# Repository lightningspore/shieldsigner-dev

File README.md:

# ShieldSigner

An open-hardware smartcard signing device built around the Luckfox Pico Mini, a 2.8-inch SPI display, and physical controls.

[Hardware](hardware/README.md) · [Build guides](docs/README.md) · [Firmware](docs/FIRMWARE-ARTIFACTS.md) · [Website](https://shieldsigner.dev/) · [Contributing](CONTRIBUTING.md)

The **main PCB is the four-layer, eight-pin display carrier with an alternate 14-pin socket in [`kicad/`](kicad/)**. Open [the KiCad project](kicad/SeedSigner-Plus-smartcard-pico.kicad_pro) to edit its schematic or layout. Its previews, assembly data, sourcing information and review reports live in [`hardware/`](hardware/README.md).

## How the pieces fit

ShieldSigner is an offline Bitcoin signer: a wallet on another machine prepares a
transaction, the signer reviews and signs it, and the result travels back by QR
code. The project has three parts:

| Part | What it is | State |
|---|---|---|
| **Hardware** | The carrier PCB in [`kicad/`](kicad/) and the printed [enclosure](docs/ENCLOSURE.md). A 240×240 display/button bench board is used for firmware development. | First-article design; digital checks pass, physical bring-up open |
| **Linux firmware** | SeedSigner OS (Buildroot) running the [LVGL frontend](firmware/lvgl-app/README.md) over the pinned ShieldSigner Python app, with the Rust camera stack in [`firmware/rkaiq-rs`](firmware/rkaiq-rs/). | Current development image, bench-tested; see [firmware status](docs/FIRMWARE-STATUS.md) |
| **Bare-metal firmware** | The same pinned app and LVGL screens on MicroPython over a Rust `no_std` runtime, with no Linux. Boots straight into the app from a ~4 MiB microSD image. | Experimental; most workflows verified on the bench board, see [`baremetal/`](baremetal/README.md) |

Both firmware paths share the application source pin, the LVGL screen library, the
Rust 3A code and the ZXing QR decoder, and both are so far qualified only on the
240×240 bench board, not on the carrier PCB.

## Current hardware

**0.0.13-dev** is a 160 × 70 mm capsule with two inner ground planes, an independently regulated display supply, eight buttons, a SEC1210 smartcard interface, and eight M2.5 mounting holes. The regulator and reader electronics are on the back. Nine factory-assembled Keystone loops provide service access, including a **GND — +5 V — GND** power clip row at 15 mm pitch.

The factory population is **44 SMT placements / 18 SKUs**, split **11 front / 33 back**. Modules, ordinary headers and mechanical hardware are fitted separately. See the [assembly guide](docs/MODULAR-ASSEMBLY.md) and [supplier-review instructions](hardware/manufacturing/README.md).

Native ERC, DRC, connectivity and schematic parity pass with zero violations or exclusions. This is a first-article development design: supplier sourcing/DFM approval and physical, thermal and powered bring-up remain open. [Order readiness](docs/PCB-ORDER-READINESS.md) tracks those limits. Older release ZIPs describe their tagged revisions; use the working tree's matched exports when reviewing 0.0.13-dev.

## Schematic and PCB views

The schematic starts with a system overview and a reading map for the six native sheets. Click a preview to open it at full resolution.

| Front PCB | Rear PCB |
|---|---|
|  |  |

[Schematic source](kicad/SeedSigner-Plus-smartcard-pico.kicad_sch) · [PCB source](kicad/SeedSigner-Plus-smartcard-pico.kicad_pcb) · [Rear assembly view](hardware/assembly-back.png)

## Open and check the board

Use [mise](https://mise.jdx.dev/) for project tasks. The project manages KiCad 10.0.7 separately from any installed KiCad 9; see [KiCad setup](KICAD.md).

```sh
mise install bun@1.2.21 uv@0.12.7
mise run setup
mise run kicad:open
mise run hardware:check
```

To regenerate review and supplier files:

```sh
mise run hardware:fab       # matched Gerbers, drills, BOM and CPL
mise run hardware:review    # schematic PDF, assembly renders, STEP and GLB
mise run hardware:package   # portable project and local review bundles
```

Outputs are written to `dist/lcd-module-2.8/`; this retained output name keeps existing tooling compatible. [`hardware/manufacturing/`](hardware/manufacturing/README.md) contains the tracked supplier data. The native project and local libraries remain the design authority.

## Build the device

| Task | Start here |
|---|---|
| Understand the circuit and pinout | [Hardware guide](docs/LCD-MODULE-VARIANT.md), [pinout and firmware compatibility](docs/PCB-SOFTWARE-COMPATIBILITY.md) |
| Source parts and assemble | [Factory kit](hardware/manufacturing/README.md), [assembly steps](docs/MODULAR-ASSEMBLY.md), [self-assembly option](docs/SELF-ASSEMBLY.md) |
| Find or build firmware | [Verified artifacts](docs/FIRMWARE-ARTIFACTS.md), [LVGL application](firmware/lvgl-app/README.md), [OS build](docs/OS-BUILD.md) |
| Try the Linux-free firmware | [Bare-metal runtime](baremetal/README.md) (experimental, bench board) |
| Print and fit the enclosure | [Enclosure guide](docs/ENCLOSURE.md), [CAD import and fit model](hardware/FIT-MODEL.md) |
| Review first-article behavior | [Display and button review](docs/DISPLAY-BUTTON-REVIEW.md), [bring-up](docs/BRINGUP.md) |
| Find component documentation | [Datasheets](datasheets/README.md) |

Use the **carrier firmware profile** before powering this PCB. The older bench profile drives two carrier button nets as display outputs. The [compatibility guide](docs/PCB-SOFTWARE-COMPATIBILITY.md) records the required 320 × 240 display configuration and GPIO mappings.

## Repository map

| Directory | Contents |
|---|---|
| [`kicad/`](kicad/) | Main native schematic, PCB, local libraries and 3D models |
| [`hardware/`](hardware/README.md) | Current-board previews, assembly files, sourcing and audits |
| [`datasheets/`](datasheets/README.md) | Component PDFs, provenance and BOM coverage |
| [`docs/`](docs/README.md) | Build, electrical, firmware and validation guides |
| [`firmware/`](firmware/) | Application, display, camera and image tooling |
| [`baremetal/`](baremetal/README.md) | Experimental Linux-free runtime: Rust drivers, MicroPython and the ported app |
| [`enclosure/`](enclosure/) | Printable enclosure and mechanical checks |
| [`scripts/`](scripts/) | Reproducible generation, export and verification tools |
| [`src/`](src/) | Experimental tscircuit projects and native reference preview |
| [`website/`](website/README.md) | Static knowledge site generated from an explicit content allowlist |
| [`variants/`](variants/README.md) | Historical FPC design and optional backlight experiment |
| [`reference/`](reference/) | Preserved upstream sources, research and attribution |

`mise run build`, `check` and `dev` use the main board's native reference preview. The independently routed tscircuit experiment has explicit `tscircuit:pill:*` tasks; it is separate from fabrication. See [port status](docs/PORT-STATUS.md).

## Attribution

Derived from [3rdIteration/SeedSigner](https://github.com/3rdIteration/seedsigner/tree/efdd1cfd14e80a076a7e1ae91e9f2270ecbcd44f/electronics/SeedSigner-Plus-smartcard-luckfoxpicozero), pinned at `efdd1cfd14e80a076a7e1ae91e9f2270ecbcd44f`. Original sources and provenance are preserved in [`reference/`](reference/provenance.json). The upstream [MIT license](LICENSE), local-library notices and supplier document attribution are retained.

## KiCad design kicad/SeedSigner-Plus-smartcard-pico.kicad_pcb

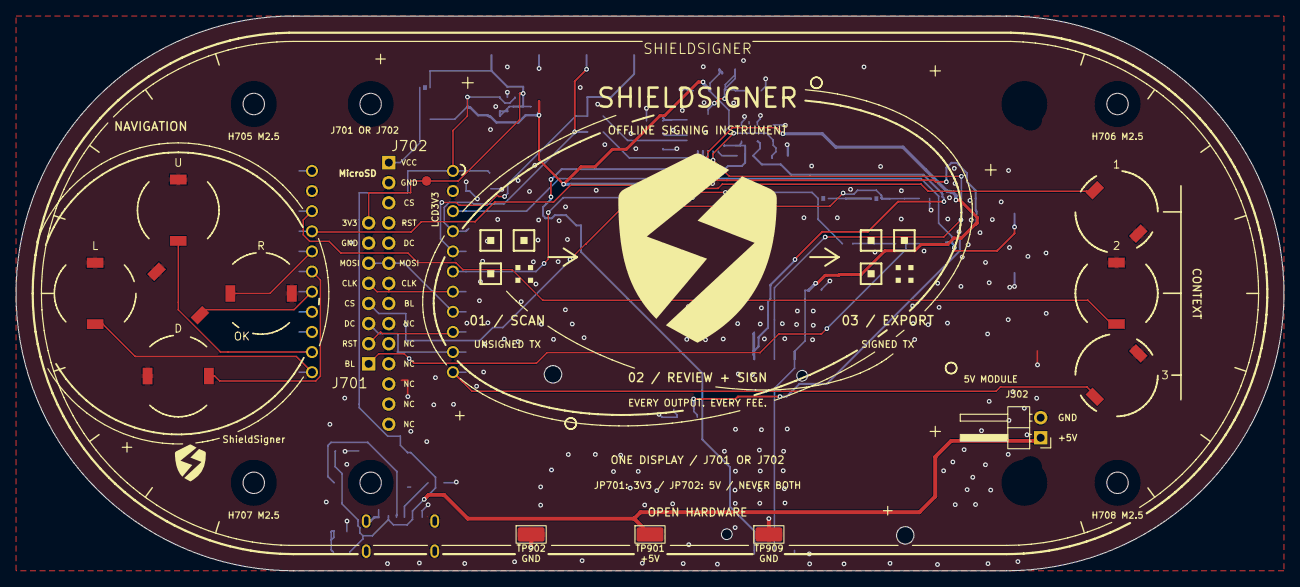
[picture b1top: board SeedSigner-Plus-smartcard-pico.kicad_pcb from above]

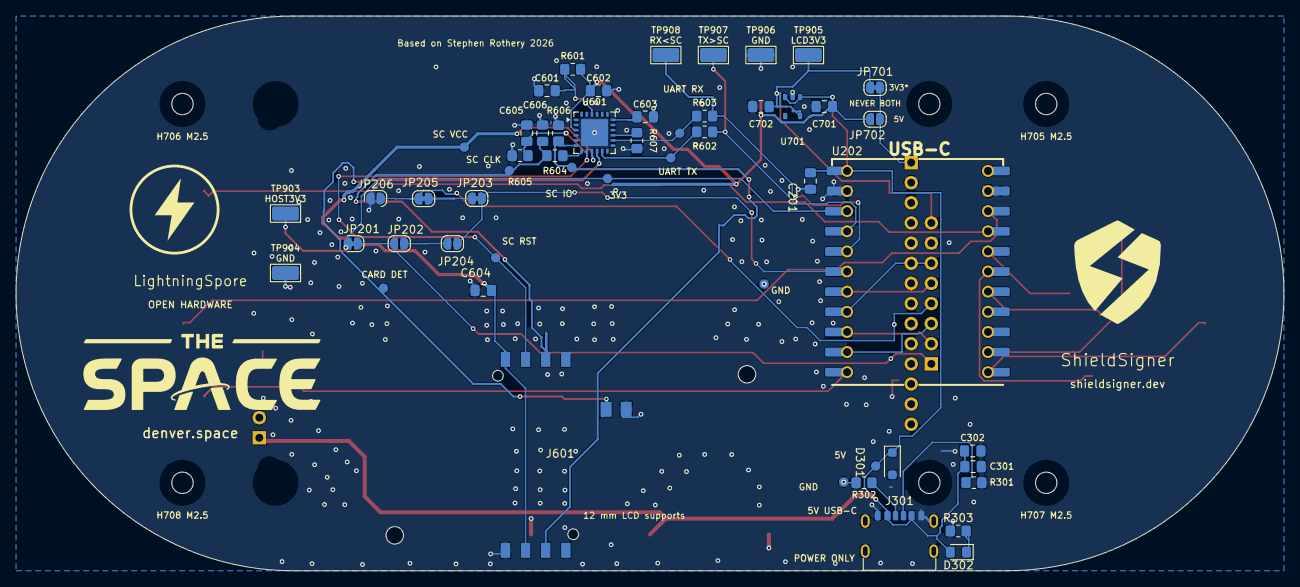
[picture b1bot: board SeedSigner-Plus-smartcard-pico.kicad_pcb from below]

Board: 4 copper layers, 160.0 x 70.0 mm, 76 parts (53 on the bottom side), 38 nets.

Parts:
C201, C302: 10u; C_0805_2012Metric_Pad1.18x1.45mm_HandSolder
C301, C601: 100n; C_0805_2012Metric_Pad1.18x1.45mm_HandSolder
C602, C603, C604: 1u; C_0805_2012Metric_Pad1.18x1.45mm_HandSolder
C605, C606: 33p; C_0805_2012Metric_Pad1.18x1.45mm_HandSolder
C701, C702: 10uF; C_0805_2012Metric_Pad1.18x1.45mm_HandSolder
D301: SMF5.0CA; D_SOD-123F
D302: KT-0805G; LED_0805_2012Metric_Pad1.15x1.40mm_HandSolder
H701, H702, H703, H704, H705, H706, H707, H708: MountingHole_2.7mm_M2.5
J301: USB4125-GF-A-0190; GCT_USB4125_GF_A
J302: 5V_MODULE; Battery5VHeader_1x02_P2.54mm_Horizontal
J601: 7312P0225A13LF; Amphenol_7312P0225A13LF_reflow
J701: LCD SPI 8-pin; LCD_SPI_8_Pill
J702: ILI9341 SPI 14-pin; LCD_SPI_14_ILI9341
JP201, JP203, JP205, JP701: Jumper_2_Small_Bridged; SolderJumper-2_P1.3mm_Bridged_RoundedPad1.0x1.5mm
JP202, JP204, JP206, JP702: Jumper_2_Small_Open; SolderJumper-2_P1.3mm_Open_RoundedPad1.0x1.5mm
R301, R302: 5K1; R_0805_2012Metric_Pad1.20x1.40mm_HandSolder
R303: 560R; R_0805_2012Metric_Pad1.20x1.40mm_HandSolder
R601, R606: 100K; R_0805_2012Metric_Pad1.20x1.40mm_HandSolder
R602, R603: 100R; R_0805_2012Metric_Pad1.20x1.40mm_HandSolder
R604: 47R; R_0805_2012Metric_Pad1.20x1.40mm_HandSolder
R605, R607: 10K; R_0805_2012Metric_Pad1.20x1.40mm_HandSolder
SW501, SW502, SW503, SW504, SW505, SW506, SW507, SW508: PTS636SK25SMTRLFS; CK_PTS636_SK25_G
TP801: 5V; TestPoint_D1.2mm
TP802: 3V3; TestPoint_D1.2mm
TP803: LCD3V3; TestPoint_D1.2mm
TP804, TP812: GND; TestPoint_D1.2mm
TP805: SC VCC; TestPoint_D1.2mm
TP806: UART RX; TestPoint_D1.2mm
TP807: UART TX; TestPoint_D1.2mm
TP808: SC CLK; TestPoint_D1.2mm
TP809: SC IO; TestPoint_D1.2mm
TP810: CARD DET; TestPoint_D1.2mm
TP811: SC RST; TestPoint_D1.2mm
TP901, TP902, TP903, TP904, TP905, TP906, TP907, TP908, TP909: 5015; Keystone_5015
U202: LuckFox_Pico_MINI; LUCKFOX_PICO_MINI_reversed
U601: SEC1210/PV-UR2; Microchip_SEC1210_QFN24_reflow
U701: AP2112K-3.3TRG1; AP2112K_SOT25_reflow

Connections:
+3.3V: JP201.1 (A), TP802.1, TP903.1, U202.3 (3V3(OUT))
+5V: C201.1, C301.1, C302.1, C602.1, C701.1, D301.1 (A1), D302.2 (A), J301.A9 (VBUS), J301.B9 (VBUS), J302.1, JP702.1, R601.2, TP801.1, TP901.1, U202.1 (VBUS), U601.3 (VDD5), U701.1, U701.3
/Smartcard Interface/SEC1210_RESET: C601.1, R601.1, U601.22 (RESET_N)
/Smartcard Interface/SEC1210_SC_CLK_PostR: C606.1, J601.C3 (CLK), R604.2, TP808.1
/Smartcard Interface/SEC1210_SC_CLK_PreR: R604.1, U601.7 (SC1_CLK)
/Smartcard Interface/SEC1210_SC_IO: J601.C7 (I/O), R606.2, TP809.1, U601.6 (SC1_IO)
/Smartcard Interface/SEC1210_SC_PRSNT: J601.NO, TP810.1, U601.10 (SC1_PRSNT_N/JTAG_TMS)
/Smartcard Interface/SEC1210_SC_RST: C605.1, J601.C2 (RST), R605.2, TP811.1, U601.8 (SC1_RST_N)
/Smartcard Interface/SEC1210_SC_VCC: C604.1, J601.C1 (VCC), J601.C6 (VPP), TP805.1, U601.9 (SC1_VCC)
/Smartcard Interface/SEC1210_VDD33: C603.1, U601.18 (VDD33)
/Smartcard Interface/UART_RX_PostR: R603.2, TP806.1, U601.14 (SPI1_MOSI/TXD)
/Smartcard Interface/UART_TX_PostR: R602.2, TP807.1, U601.11 (SPI1_MISO/RXD)
GND: C201.2, C301.2, C302.2, C601.2, C602.2, C603.2, C604.2, C605.2, C606.2, C701.2, C702.2, D301.2 (A2), J301.A12 (GND), J301.B12 (GND), J301.S1 (SHIELD), J302.2, J601.C5 (GND), J601.COM, J701.7, J702.2, JP206.1 (A), R301.2, R302.2, R303.1, R605.1, R606.1, R607.1, SW501.2, SW502.2, SW503.2, SW504.2, SW505.2, SW506.2, SW507.2, SW508.2, TP804.1, TP812.1, TP902.1, TP904.1, TP906.1, TP909.1, U202.2 (GND), U202.21 (GND), U601.25 (GND), U701.2
JoystickDown: SW504.1, U202.17 (GPIO1_C7_d)
JoystickLeft: SW501.1, U202.12 (GPIO1_D0_d)
JoystickPress: SW503.1, U202.16 (GPIO1_C6_d)
JoystickRight: SW505.1, U202.18 (GPIO0_A4_d)
JoystickUp: SW502.1, U202.13 (GPIO1_D1_d)
Key1: SW506.1, U202.19 (GPIO4_C0_z)
Key2: SW507.1, U202.20 (GPIO4_C1_z)
Key3: SW508.1, U202.11 (GPIO1_C5_d)
LCD_3V3: C702.1, J701.8, JP701.1, TP803.1, TP905.1, U701.5
LCD_ALT_VCC: J702.1, JP701.2, JP702.2
LCD_DC: J701.3, J702.5, U202.10 (GPIO1_C4_d)
LCD_MOSI: J701.6, J702.6, U202.8 (SPI0_MOSI_M0/GPIO1_C2_d)
LCD_RST: J701.2, J702.4, U202.9 (SPI0_MISO_M0/GPIO1_C3_d)
LCD_SCLK: J701.5, J702.7, U202.7 (SPI0_CLK_M0/IO1_C1_d)
MCU_BACKLIGHT: JP202.1 (A), JP204.1 (A)
MCU_SPI_CS: JP203.1 (A), JP205.1 (A)
unnamed: D302.1 (K), R303.2
unnamed: J301.A5 (CC1), R302.1
unnamed: J301.B5 (CC2), R301.1
unnamed: JP203.2 (B), JP204.2 (B), U202.6 (SPI0_CS0_M0/IO1_C0_d)
unnamed: R607.2, U601.15 (TEST)
RPI_BACKLIGHT: J701.1, J702.8, JP201.2 (B), JP202.2 (B)
RPI_SPI_CS: J701.4, J702.3, JP205.2 (B), JP206.2 (B)
UART_RX: R603.1, TP908.1, U202.5 (GPIO1_B3_u)
UART_TX: R602.1, TP907.1, U202.4 (GPIO1_B2_d)

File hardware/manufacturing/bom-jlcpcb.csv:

Comment,Designator,Footprint,LCSC Part #
33 pF; CC0805JRNPO9BN330,"C605,C606",C_0805_2012Metric_Pad1.18x1.45mm_HandSolder,C107115
100 kΩ; 0805W8F1003T5E,"R601,R606",R_0805_2012Metric_Pad1.20x1.40mm_HandSolder,C149504
10 µF; CL21A106KAYNNNE,"C201,C302,C701,C702",C_0805_2012Metric_Pad1.18x1.45mm_HandSolder,C15850
100 Ω; 0805W8F1000T5E,"R602,R603",R_0805_2012Metric_Pad1.20x1.40mm_HandSolder,C17408
10 kΩ; 0805W8F1002T5E,"R605,R607",R_0805_2012Metric_Pad1.20x1.40mm_HandSolder,C17414
47 Ω; 0805W8F470JT5E,R604,R_0805_2012Metric_Pad1.20x1.40mm_HandSolder,C17714
SMF5.0CA; SMF5.0CA,D301,D_SOD-123F,C19077498
KT-0805G; KT-0805G,D302,LED_0805_2012Metric_Pad1.15x1.40mm_HandSolder,C2297
PTS636SK25SMTRLFS; PTS636SK25SMTRLFS,"SW501,SW502,SW503,SW504,SW505,SW506,SW507,SW508",CK_PTS636_SK25_G,C2689642
5.1 kΩ; 0805W8F5101T5E,"R301,R302",R_0805_2012Metric_Pad1.20x1.40mm_HandSolder,C27834
1 µF; CL21B105KBFNNNE,"C602,C603,C604",C_0805_2012Metric_Pad1.18x1.45mm_HandSolder,C28323
560 Ω; 0805W8F5600T5E,R303,R_0805_2012Metric_Pad1.20x1.40mm_HandSolder,C28636
5015; 5015,"TP901,TP902,TP903,TP904,TP905,TP906,TP907,TP908,TP909",Keystone_5015,C2906768
100 nF; CC0805KRX7R9BB104,"C301,C601",C_0805_2012Metric_Pad1.18x1.45mm_HandSolder,C49678
AP2112K-3.3TRG1; AP2112K-3.3TRG1,U701,AP2112K_SOT25_reflow,C51118
USB4125-GF-A-0190; USB4125-GF-A-0190,J301,GCT_USB4125_GF_A,C5246813
7312P0225A13LF; 7312P0225A13LF,J601,Amphenol_7312P0225A13LF_reflow,C5417011
SEC1210/PV-UR2; SEC1210/PV-UR2,U601,Microchip_SEC1210_QFN24_reflow,C633309

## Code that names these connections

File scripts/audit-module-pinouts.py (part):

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alternate = ['LCD_ALT_VCC', 'GND', 'RPI_SPI_CS', 'LCD_RST', 'LCD_DC', 'LCD_MOSI', 'LCD_SCLK', 'RPI_BACKLIGHT']
assert [pins['J702'][str(i)] for i in range(1, 9)] == alternate
assert all(pins['J702'][str(i)].startswith('unconnected-') for i in range(9, 15))
assert pins['JP701'] == {'1': 'LCD_3V3', '2': 'LCD_ALT_VCC'}
assert pins['JP702'] == {'1': '+5V', '2': 'LCD_ALT_VCC'}
assert 'Bridged' in fps['JP701'][1] and '_Open_' in fps['JP702'][1]
assert 'dnp' in one(fps['J702'], 'attr')
graph = collections.defaultdict(set)
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for ref, rail in [('C701', '+5V'), ('C702', 'LCD_3V3')]:
    assert pins[ref] == {'1': rail, '2': 'GND'}
assert pins['J302']=={'1':'+5V','2':'GND'}
for ref,net in [('TP901','+5V'),('TP902','GND'),('TP909','GND'),('TP903','+3.3V'),('TP905','LCD_3V3'),('TP907','UART_TX'),('TP908','UART_RX')]:assert pins[ref]=={'1':net}
for p in ('14', '15', '22'):
    assert nets[pins['U202'][p]] == {f'U202.{p}'}, p
# Check every key, not only the two 1.8 V inputs. Exact net membership rejects
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# and the numbered socket contacts agree with the selected native channel.
sc = '/Smartcard Interface/'
assert pins['U601']['3'] == '+5V' and pins['U601']['25'] == 'GND'
assert pins['U601']['18'] == sc+'SEC1210_VDD33'
assert pins['U601']['9'] == sc+'SEC1210_SC_VCC'
assert not connected(sc+'SEC1210_VDD33', '+3.3V')
assert not connected(sc+'SEC1210_SC_VCC', '+3.3V')
for ref, rail in [('C602','+5V'),('C603',sc+'SEC1210_VDD33'),('C604',sc+'SEC1210_SC_VCC')]:
    assert pins[ref] == {'1':rail,'2':'GND'}
    value = next(p[2] for p in children(fps[ref],'property') if p[1]=='Value')
    assert value == '1u', (ref,'reader requires nominal 1uF decoupling')
assert pins['J601'] == {'C1':sc+'SEC1210_SC_VCC','C2':sc+'SEC1210_SC_RST',
                       'C3':sc+'SEC1210_SC_CLK_PostR','C4':'unconnected-(J601-RFU-PadC4)',
                       'C5':'GND','C6':sc+'SEC1210_SC_VCC','C7':sc+'SEC1210_SC_IO',
                       'C8':'unconnected-(J601-RFU__1-PadC8)',
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assert pins['U601']['6'] == pins['J601']['C7']
assert pins['U601']['8'] == pins['J601']['C2']
assert pins['U601']['10'] == pins['J601']['NO']
assert pins['R604'] == {'1':sc+'SEC1210_SC_CLK_PreR','2':sc+'SEC1210_SC_CLK_PostR'}
assert pins['U601']['7'] == pins['R604']['1']
assert next(p[2] for p in children(fps['U601'],'property') if p[1]=='Value') == 'SEC1210/PV-UR2'

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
